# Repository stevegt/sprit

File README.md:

# sprit

I/O interface between a Raspberry Pi and a Dynamixel XL-320 servo.
Other Dynamixel models may work too, as well as other serial bus
servos such as those from Hiwonder -- haven't tested.

The Sprit is similar to the Poppy Project's Pixl board:

- https://www.poppy-project.org/en/
- https://github.com/poppy-project/pixl/blob/master/circuit_maker/Pixl.PDF

The main differences between the Sprit and Pixl are in the power
subsystem -- the Sprit is optimized for stationary use, while the Pixl
is optimized for mobile use on batteries:

| load      | Sprit                | Pixl                        |
|-----------|----------------------|-----------------------------|
| Pi        | USB                  | 7V barrel jack or batteries |
| 7V servos |                      | 7V barrel jack or batteries |
| 8V servos | 10.5-18V barrel jack |                             |

- Sprit accepts anything from 10.5 to 18V via the barrel jack and
  regulates that down to 8V power for the servos.  Sprit does not
  provide power for the Pi, so the Pi must be powered via USB.
- Pixl accepts 7V from barrel jack or batteries, passes that
  unregulated to the servos, and regulates it down to 5V to power the
  Pi, so the Pi does not need to be plugged into USB power.

## Oshpark prototype v0.2 bare board

<a href="https://oshpark.com/shared_projects/FYFJ6RjU"></img></a>

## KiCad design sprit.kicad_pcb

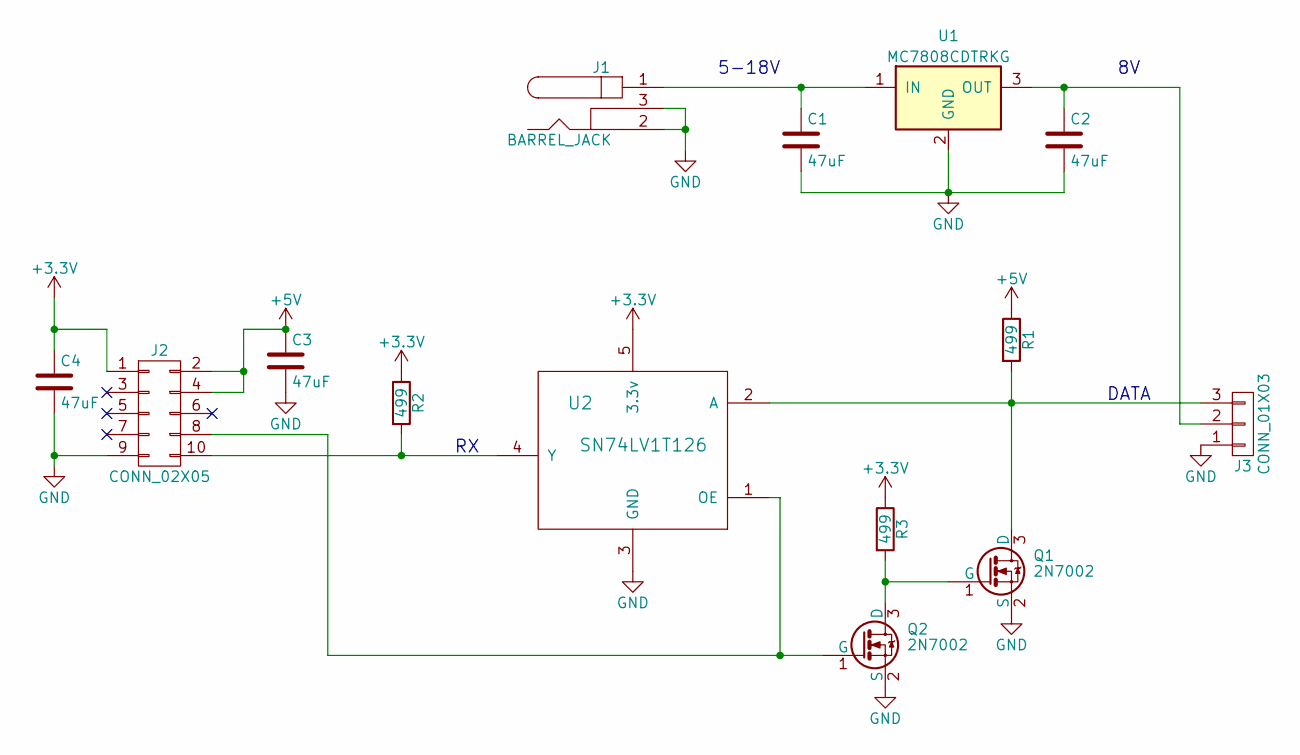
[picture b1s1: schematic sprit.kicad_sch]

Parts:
C1, C2, C3, C4: 47uF; C_1206_3216Metric
J1: BARREL_JACK; BarrelJack_Horizontal
J2: CONN_02X05; PinHeader_2x05_P2.54mm_Vertical
J3: CONN_01X03; Molex_Micro-Latch_53254-0370_1x03_P2.00mm_Horizontal
Q1, Q2: 2N7002; SOT-23
R1, R2, R3: 499; R_0805_2012Metric
U1: MC7808CDTRKG; TO-252-2
U2: SN74LV1T126; SOT-23-5

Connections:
+3V3: C4.1, J2.1, R2.1, R3.1, U2.5 (3.3v)
+5V: C3.1, J2.2, J2.4, R1.1
GND: C1.2, C2.2, C3.2, C4.2, J1.2, J1.3, J2.9, J3.1, Q1.2 (S), Q2.2 (S), U1.2 (GND), U2.3 (GND)
unnamed: C1.1, J1.1, U1.1 (IN)
unnamed: C2.1, J3.2, U1.3 (OUT)
unnamed: J2.8, Q2.1 (G), U2.1 (OE)
unnamed: J2.10, R2.2, U2.4 (Y)
unnamed: J3.3, Q1.3 (D), R1.2, U2.2 (A)
unnamed: Q1.1 (G), Q2.3 (D), R3.2

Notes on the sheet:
DATA
5-18V

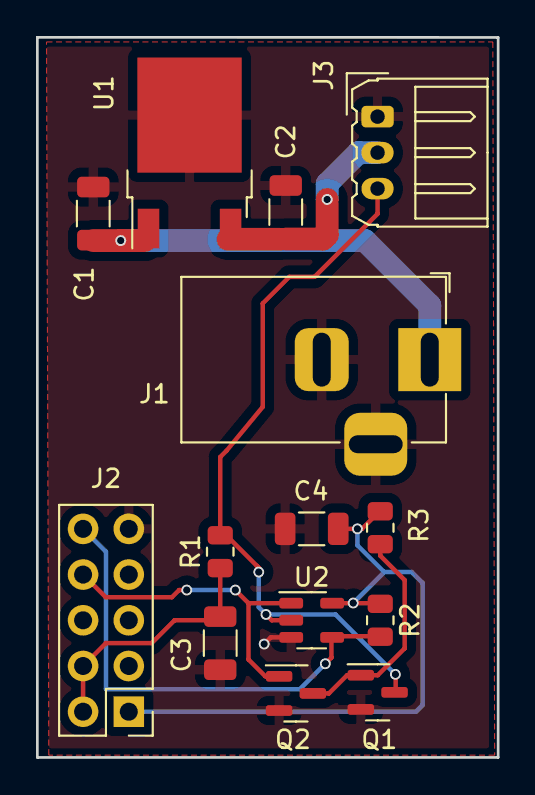
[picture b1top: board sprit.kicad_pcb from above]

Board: 2 copper layers, 25.6 x 40.0 mm, 14 parts (0 on the bottom side), 9 nets.

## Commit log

2018-08-13 import of first alpha version as built
2022-09-17 WIP rework layout
    - checkpoint of 2018 changes found in repo
    - used kicad 4.0.7 as of 2018
    - apparent work in progress:
    - enlarge board
    - recess barrel jack
    - move J3 connector to opposite edge
2022-09-17 finish layout rework started 4 years ago(!)
    - recess barrel jack
    - move J3 connector to opposite edge
2022-09-18 upgrade to kicad 6.0.7
    - v0.2 as ordered from oshpark
    - replace footprints
    - add pdf of 2017 mouser order
2022-09-18 fix supply voltage notation, add README
